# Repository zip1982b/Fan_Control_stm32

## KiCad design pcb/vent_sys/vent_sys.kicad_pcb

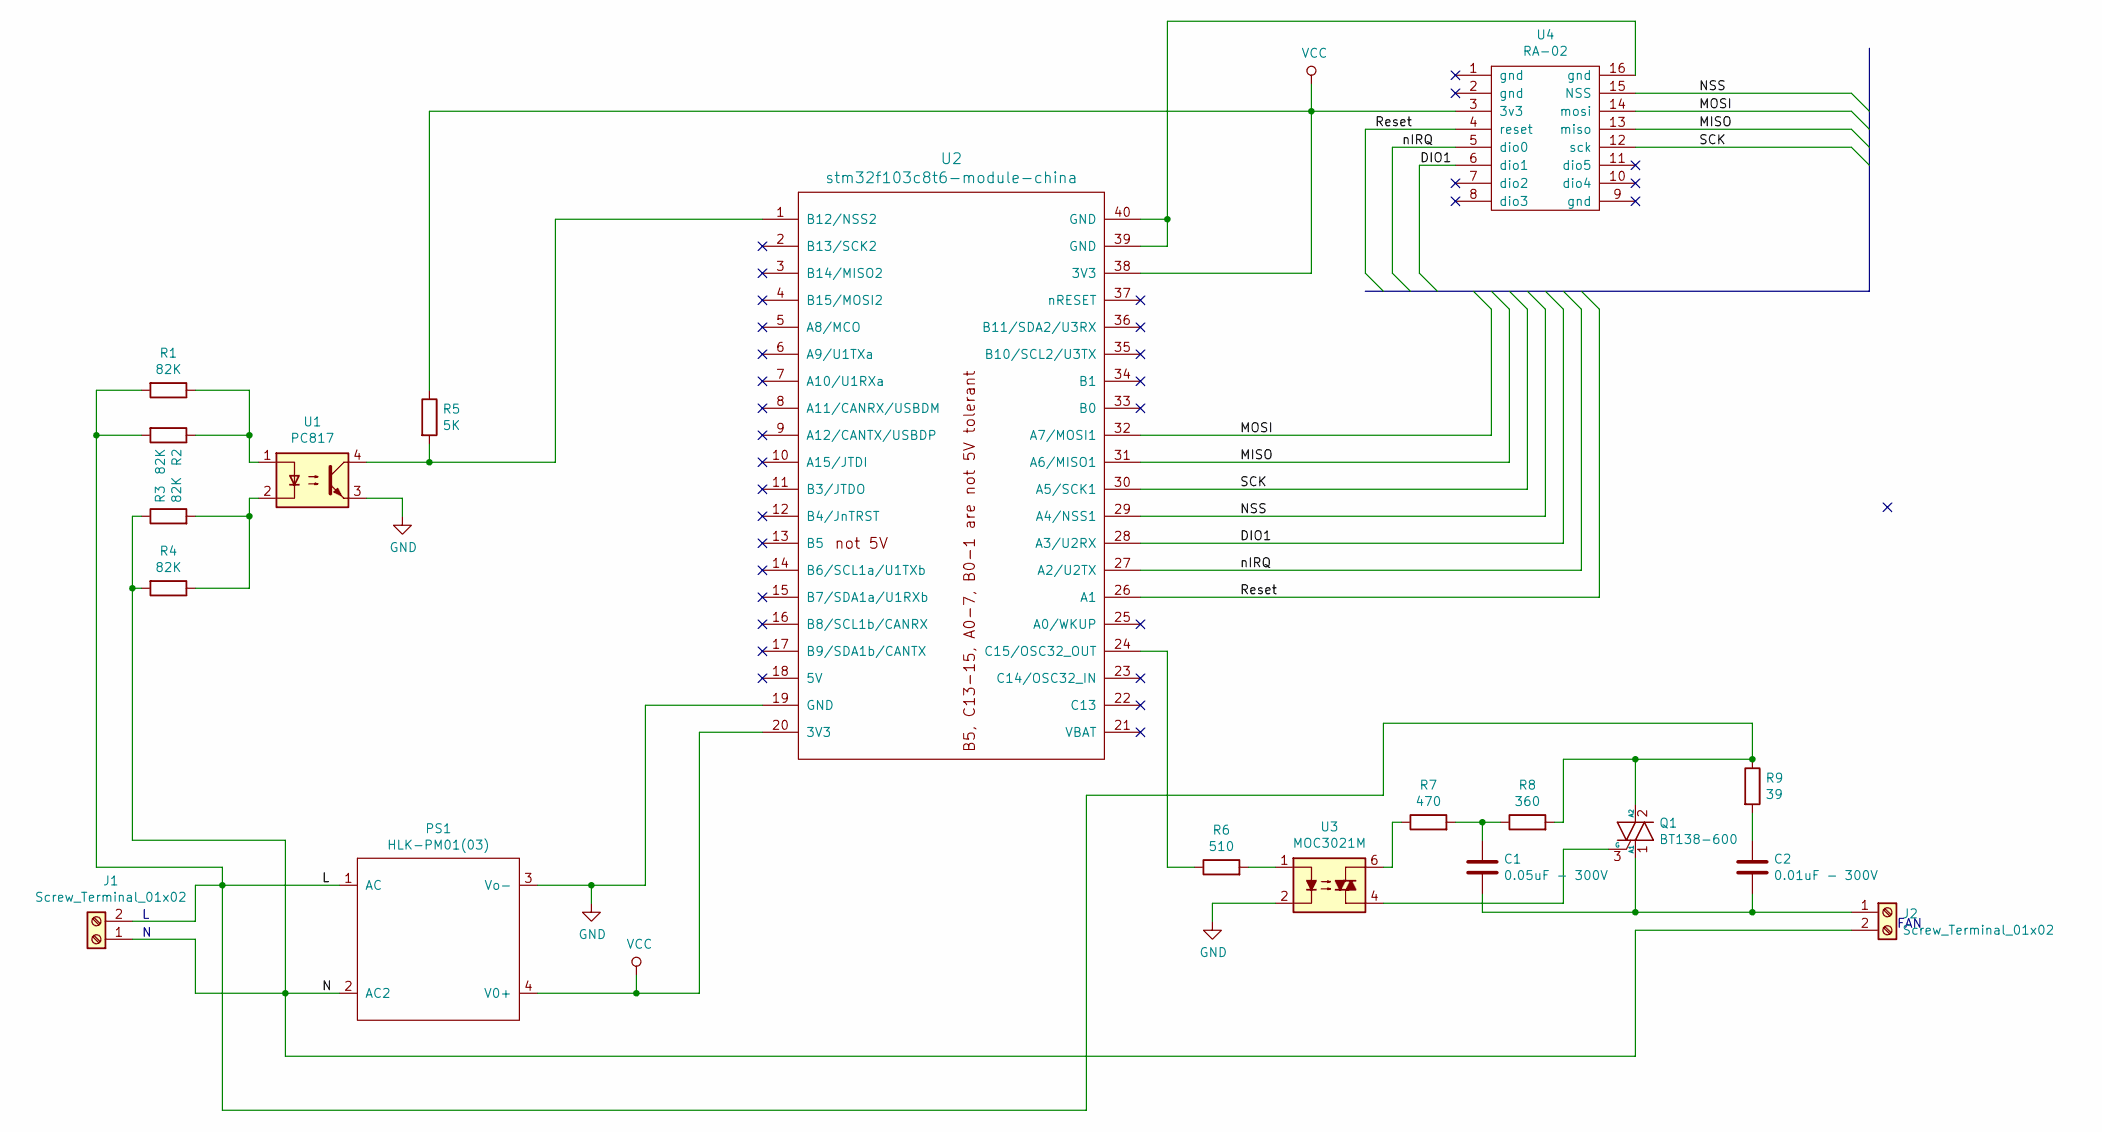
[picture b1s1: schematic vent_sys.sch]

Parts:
C1: 0.05uF - 300V; C_Rect_L10.0mm_W2.5mm_P7.50mm_MKS4
C2: 0.01uF - 300V; C_Rect_L9.0mm_W3.2mm_P7.50mm_MKT
J1, J2: Screw_Terminal_01x02; PhoenixContact_MCV_1,5_2-G-5.08_1x02_P5.08mm_Vertical
PS1: HLK-PM01(03); HLK-PM01
Q1: BT138-600; TO-220-3_Vertical
R1, R2, R3, R4: 82K; R_Axial_DIN0207_L6.3mm_D2.5mm_P10.16mm_Horizontal
R5: 5K; R_0805_2012Metric_Pad1.15x1.40mm_HandSolder
R6: 510; R_0805_2012Metric_Pad1.15x1.40mm_HandSolder
R7: 470; R_Axial_DIN0207_L6.3mm_D2.5mm_P10.16mm_Horizontal
R8: 360; R_Axial_DIN0207_L6.3mm_D2.5mm_P10.16mm_Horizontal
R9: 39; R_Axial_DIN0207_L6.3mm_D2.5mm_P10.16mm_Horizontal
U1: PC817; DIP-4_W7.62mm
U2: stm32f103c8t6-module-china; Maple_Mini
U3: MOC3021M; DIP-6_W10.16mm
U4: RA-02; Ai-Thinker-Ra-01-LoRa

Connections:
/DIO1: U2.28 (A3/U2RX), U4.6 (dio1)
/L: J1.2, PS1.1 (AC), Q1.2 (A2), R1.2, R2.2, R8.2, R9.1
/MISO: U2.31 (A6/MISO1), U4.13 (miso)
/MOSI: U2.32 (A7/MOSI1), U4.14 (mosi)
/N: J1.1, J2.2, PS1.2 (AC2), R3.1, R4.2
/NSS: U2.29 (A4/NSS1), U4.15 (NSS)
/Reset: U2.26 (A1), U4.4 (reset)
/SCK: U2.30 (A5/SCK1), U4.12 (sck)
/nIRQ: U2.27 (A2/U2TX), U4.5 (dio0)
GND: PS1.3 (Vo-), U1.3, U2.19 (GND), U3.2
unnamed: C1.1, R7.2, R8.1
unnamed: C1.2, C2.2, J2.1, Q1.1 (A1)
unnamed: C2.1, R9.2
unnamed: Q1.3 (G), U3.4
unnamed: R1.1, R2.1, U1.1
unnamed: R3.2, R4.1, U1.2
unnamed: R5.2, U1.4, U2.1 (B12/NSS2)
unnamed: R6.1, U2.24 (C15/OSC32_OUT)
unnamed: R6.2, U3.1
unnamed: R7.1, U3.6
unnamed: U2.39 (GND), U2.40 (GND), U4.16 (gnd)
VCC: PS1.4 (V0+), R5.1, U2.20 (3V3), U2.38 (3V3), U4.3 (3v3)

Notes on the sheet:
FAN

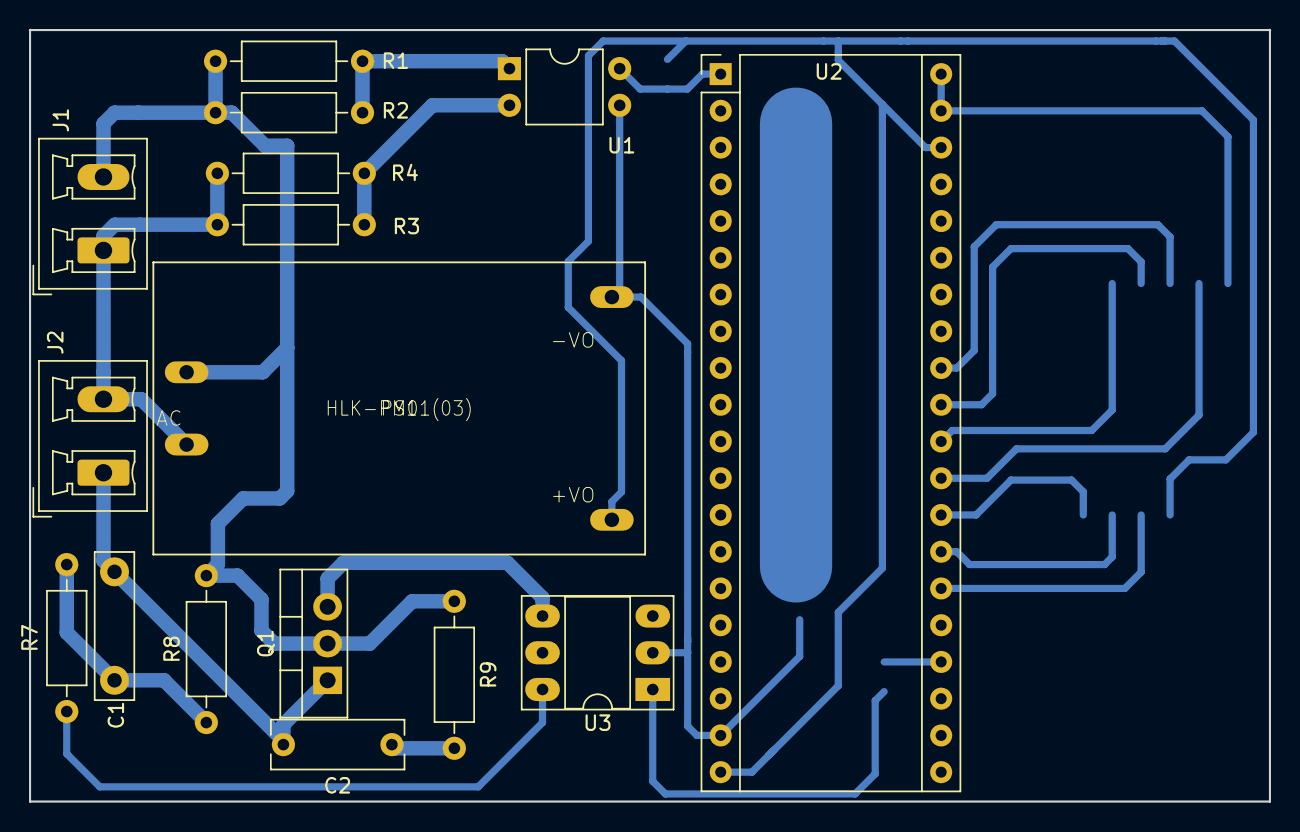
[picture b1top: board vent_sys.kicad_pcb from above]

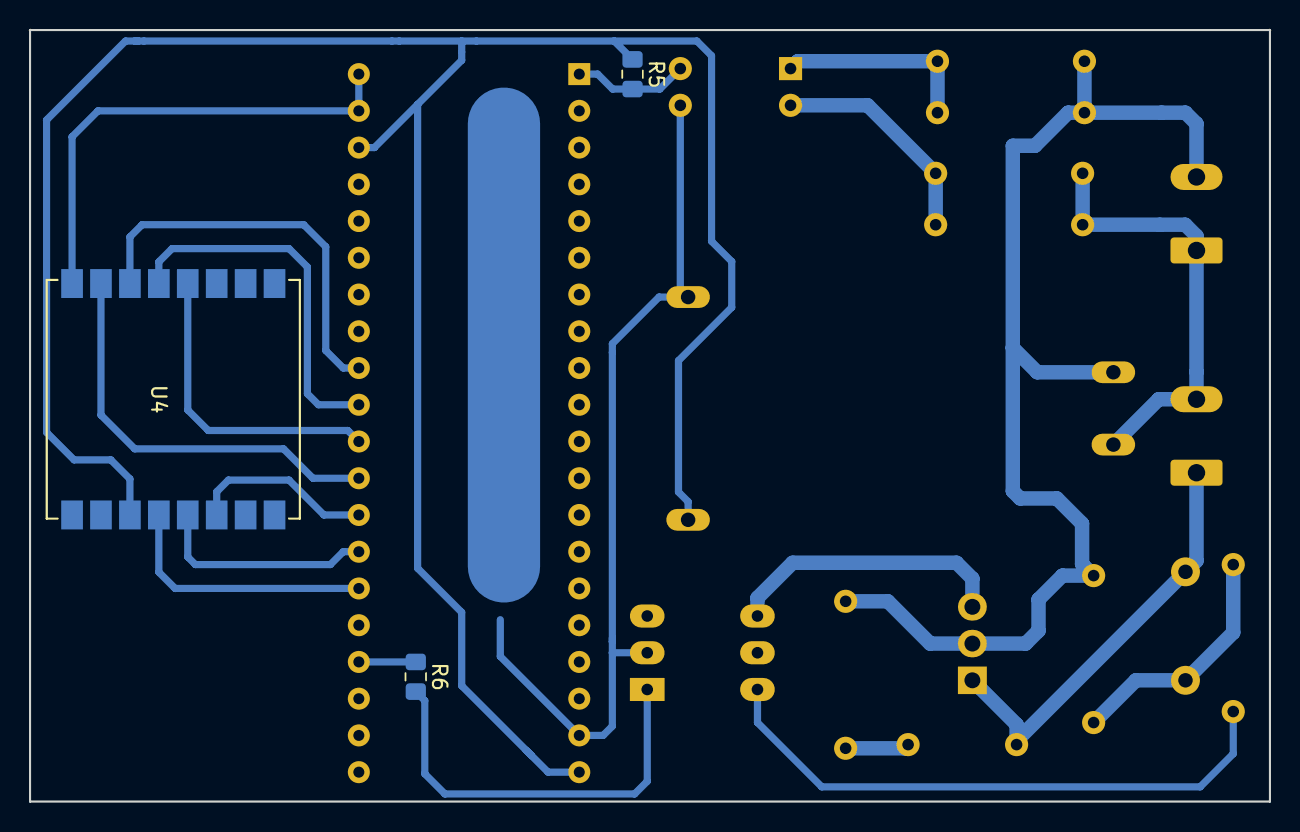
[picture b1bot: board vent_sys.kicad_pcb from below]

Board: 2 copper layers, 85.7 x 53.3 mm, 19 parts (3 on the bottom side), 22 nets.

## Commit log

2019-03-16 first commit, tested ext interrupt, tested triac
2019-03-16 add gitignore
2019-03-19 before new branch
2019-03-19 deleted ds2482-100
2019-03-19 connect RA02
2019-03-20 add unique identifiers
2019-03-20 electrical rules check are OK
2019-03-20 add net list and foot prints
2019-03-24 pcb trace
2019-03-27 PCB trace completed
2019-03-27 add Gerber files
2019-04-01 final
2019-05-06 edit tasks
